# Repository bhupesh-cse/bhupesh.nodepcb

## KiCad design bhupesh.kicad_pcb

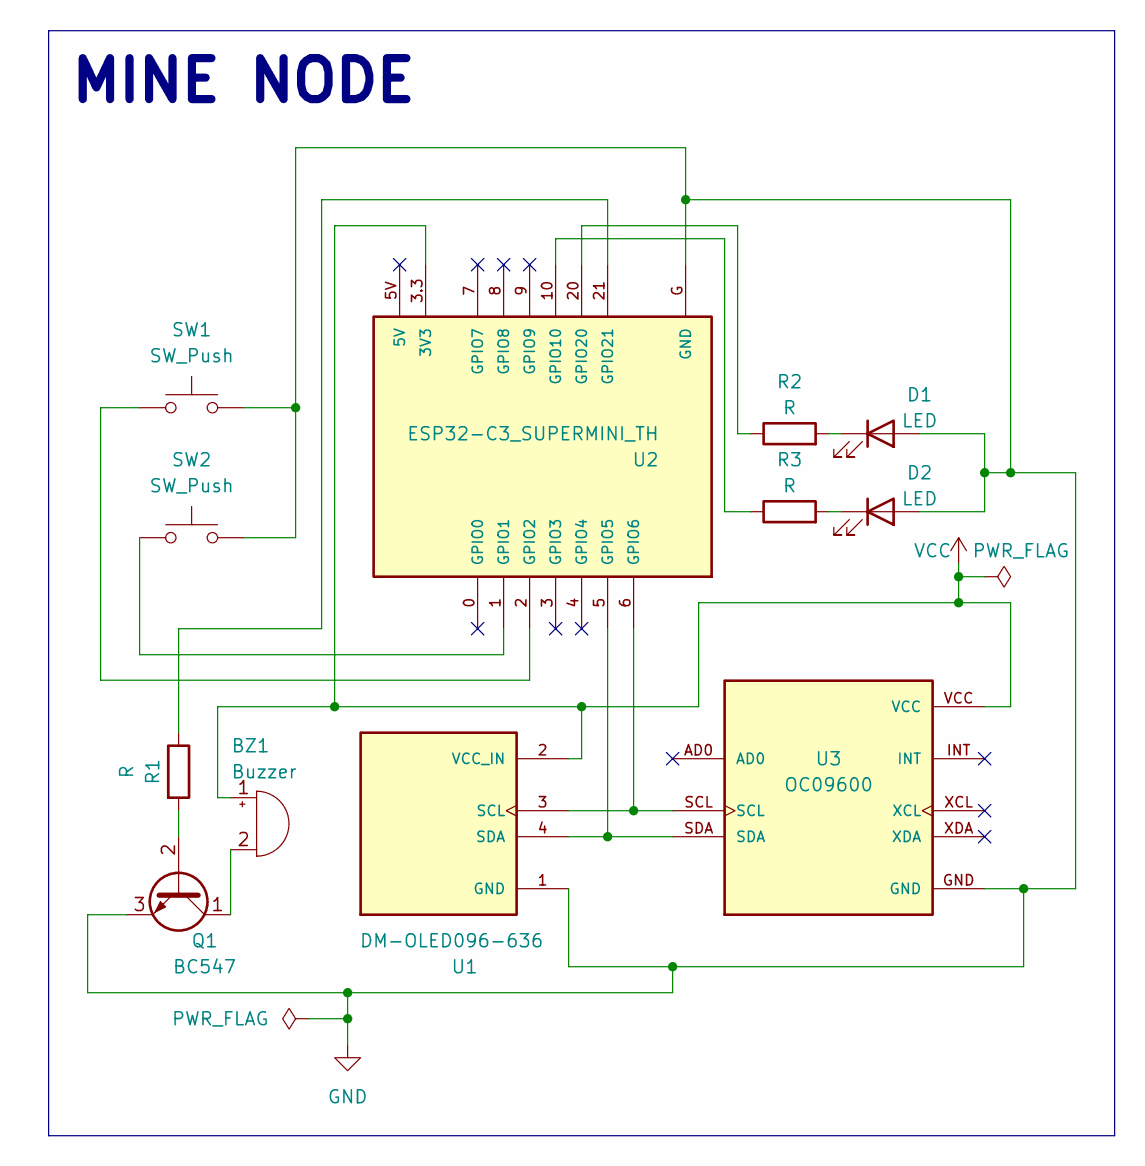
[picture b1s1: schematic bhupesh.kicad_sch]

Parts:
BZ1: Buzzer; Buzzer_12x9.5RM7.6
D1, D2: LED; LED_D5.0mm
Q1: BC547; TO-92_Inline
R1, R2, R3: R; R_Axial_DIN0207_L6.3mm_D2.5mm_P2.54mm_Vertical
SW1, SW2: SW_Push; SW_PUSH_6mm
U1: DM-OLED096-636; MODULE_DM-OLED096-636; PARTREV 2018-09-10
U2: ESP32-C3_SUPERMINI_TH; MODULE_ESP32-C3_SUPERMINI_TH
U3: OC09600; MODULE_OC09600; PARTREV NA

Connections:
GND: D1.2 (A), D2.2 (A), Q1.3 (E), SW1.2, SW2.2, U1.1 (GND), U2.G (GND), U3.GND
unnamed: BZ1.2 (-), Q1.1 (C)
unnamed: D1.1 (K), R2.2
unnamed: D2.1 (K), R3.2
unnamed: Q1.2 (B), R1.2
unnamed: U1.3 (SCL), U2.6 (GPIO6), U3.SCL
unnamed: U1.4 (SDA), U2.5 (GPIO5), U3.SDA
unnamed: SW2.1, U2.1 (GPIO1)
unnamed: SW1.1, U2.2 (GPIO2)
unnamed: R3.1, U2.10 (GPIO10)
unnamed: R2.1, U2.20 (GPIO20)
unnamed: R1.1, U2.21 (GPIO21)
VCC: BZ1.1 (+), U1.2 (VCC_IN), U2.3.3 (3V3), U3.VCC

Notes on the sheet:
MINE NODE

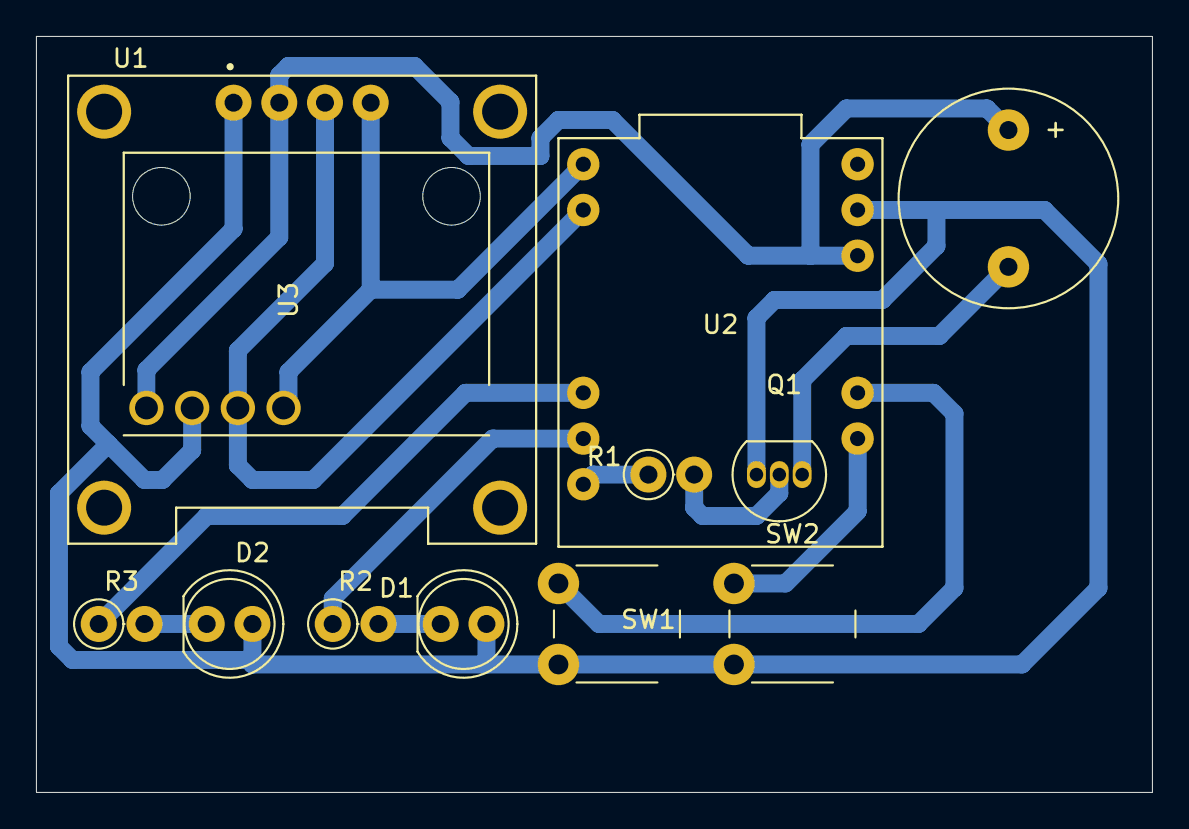
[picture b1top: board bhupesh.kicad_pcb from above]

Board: 2 copper layers, 62.0 x 42.0 mm, 12 parts (0 on the bottom side), 13 nets.

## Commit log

2026-06-12 Updated project
